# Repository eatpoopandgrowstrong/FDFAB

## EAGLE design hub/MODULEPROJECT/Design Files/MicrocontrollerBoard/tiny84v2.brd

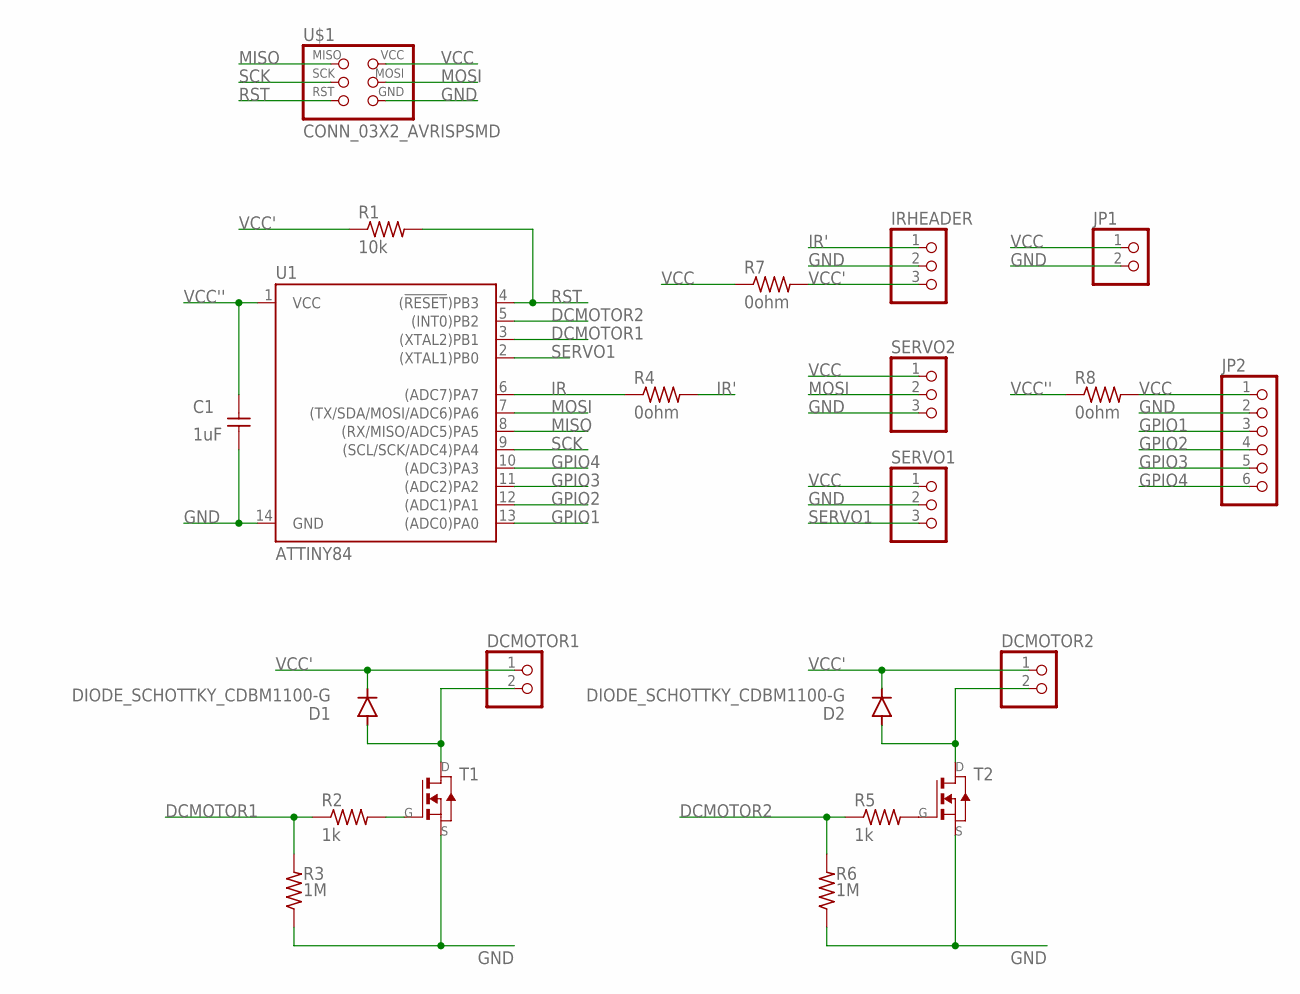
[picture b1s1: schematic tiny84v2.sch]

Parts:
C1: 1uF; C1206FAB
D1, D2: DIODE_SCHOTTKY_CDBM1100-G; MINI-SMA
DCMOTOR1, DCMOTOR2: PINHD-1X2; 1X02
IRHEADER: PINHD-1X3; 1X03
JP1: PINHD-1X2; 1X02
JP2: PINHD-1X6; 1X06
R1: 10k; R1206FAB
R2, R5: 1k; R1206FAB
R3, R6: 1M; R1206FAB
R4, R7, R8: 0ohm; R1206FAB
SERVO1, SERVO2: PINHD-1X3; 1X03
T1, T2: MOSFET_NSOT23; SOT-23
U1: ATTINY84; SO14
U$1: CONN_03X2_AVRISPSMD; 2X03SMD

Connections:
DCMOTOR1: R2.1, R3.2, U1.3 ((XTAL2)PB1)
DCMOTOR2: R5.1, R6.2, U1.5 ((INT0)PB2)
GND: C1.1, IRHEADER.2, JP1.2, JP2.2, R3.1, R6.1, SERVO1.2, SERVO2.3, T1.2 (S), T2.2 (S), U1.14 (GND), U$1.6 (GND)
GPIO1: JP2.3, U1.13 ((ADC0)PA0)
GPIO2: JP2.4, U1.12 ((ADC1)PA1)
GPIO3: JP2.5, U1.11 ((ADC2)PA2)
GPIO4: JP2.6, U1.10 ((ADC3)PA3)
IR: R4.1, U1.6 ((ADC7)PA7)
IR': IRHEADER.1, R4.2
MISO: U1.8 ((RX/MISO/ADC5)PA5), U$1.1 (MISO)
MOSI: SERVO2.2, U1.7 ((TX/SDA/MOSI/ADC6)PA6), U$1.4 (MOSI)
unnamed: D2.ANODE, DCMOTOR2.2, T2.1 (D)
unnamed: D1.ANODE, DCMOTOR1.2, T1.1 (D)
unnamed: R2.2, T1.3 (G)
unnamed: R5.2, T2.3 (G)
RST: R1.2, U1.4 ((!RESET!)PB3), U$1.5 (RST)
SCK: U1.9 ((SCL/SCK/ADC4)PA4), U$1.3 (SCK)
SERVO1: SERVO1.3, U1.2 ((XTAL1)PB0)
VCC: JP1.1, JP2.1, R7.1, R8.2, SERVO1.1, SERVO2.1, U$1.2 (VCC)
VCC': D1.KATHODE, D2.KATHODE, DCMOTOR1.1, DCMOTOR2.1, IRHEADER.3, R1.1, R7.2
VCC'': C1.2, R8.1, U1.1 (VCC)

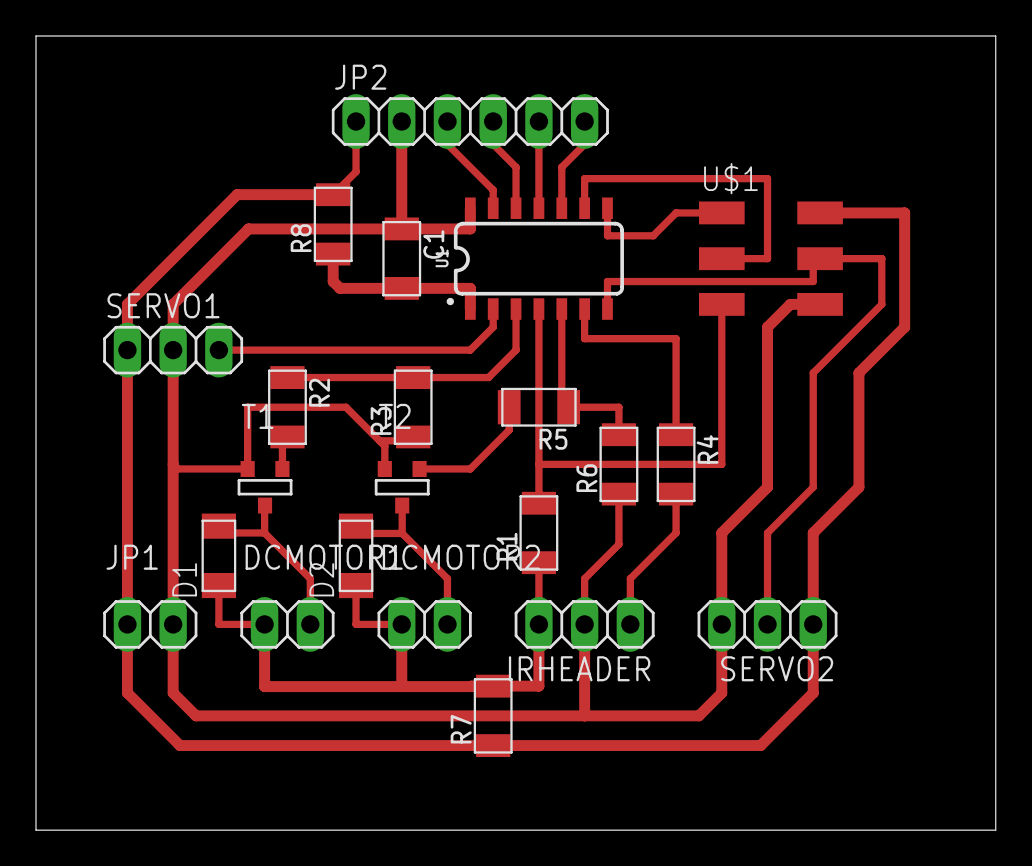
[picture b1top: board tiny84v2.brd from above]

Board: 2 copper layers, 53.3 x 44.1 mm, 22 parts (0 on the bottom side), 21 nets.

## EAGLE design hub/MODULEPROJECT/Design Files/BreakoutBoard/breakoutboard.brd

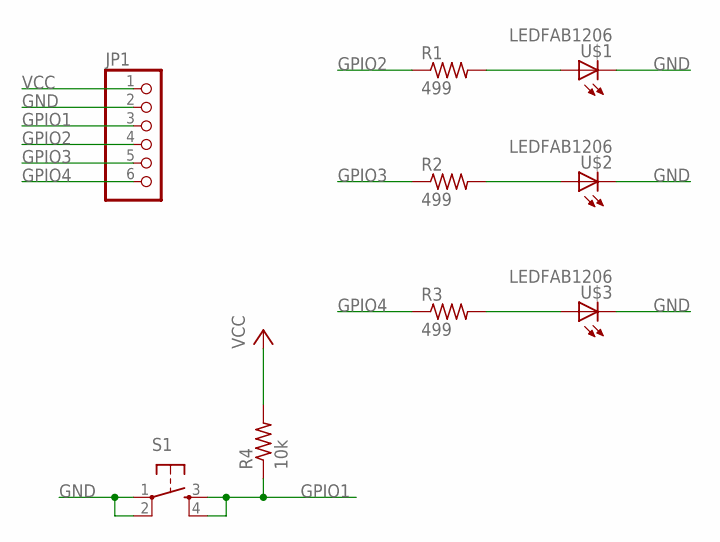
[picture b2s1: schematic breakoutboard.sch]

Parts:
JP1: PINHD-1X6; 1X06
R1, R2, R3: 499; R1206FAB
R4: 10k; R1206FAB
S1: SW_SWITCH_TACTILE_6MM6MM_SWITCH; 6MM_SWITCH
U$1, U$2, U$3: LEDFAB1206; LED1206FAB

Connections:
GND: JP1.2, S1.1, S1.2 (P1), U$1.2 (C), U$2.2 (C), U$3.2 (C)
GPIO1: JP1.3, R4.1, S1.3 (S), S1.4 (S1)
GPIO2: JP1.4, R1.1
GPIO3: JP1.5, R2.1
GPIO4: JP1.6, R3.1
unnamed: R1.2, U$1.1 (A)
unnamed: R2.2, U$2.1 (A)
unnamed: R3.2, U$3.1 (A)
VCC: JP1.1, R4.2

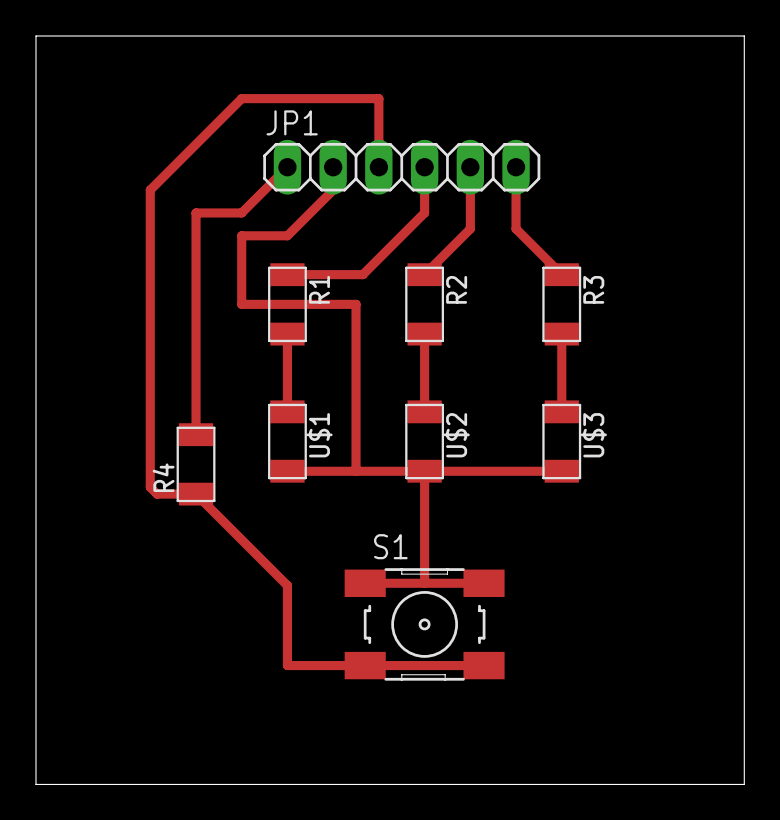
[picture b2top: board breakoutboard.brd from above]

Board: 2 copper layers, 39.4 x 41.6 mm, 9 parts (0 on the bottom side), 9 nets.

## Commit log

2021-01-24 3d machining content and images
2021-01-24 more 3d cnc content and images
2021-01-24 datasheet content and images
2021-01-24 embedded programming files and content
2021-01-24 pushbuttonLED content image and video
2021-01-25 nav bar fix and content
2021-01-25 ino codes as well as content update
2021-01-25 content for processing light bulb aas well as 3d machining stuff
2021-01-25 code for processing serial arduino
2021-01-25 MOAR CONTENT
2021-01-25 updates to images and content
2021-01-25 Slight edit to content as well as 3d machining .nc file
2021-01-25 post processing images and edits to content
2021-01-26 most post processing content and their images
2021-01-28 Embedded programming/processing videos
2021-01-28 updated to show vids
2021-01-28 test fix
2021-01-28 yolo
2021-01-28 Revert "yolo"
    This reverts commit a2d682e73cf3cb537754ce7032bcc7a5690a3578.
2021-01-29 proposal update
2021-01-29 update to nav bar
2021-01-30 3D machining and moldingandcasting content
2021-01-30 moldingandcasting content and videos
2021-01-30 moldandcasting content and images
2021-01-30 more content
2021-01-31 proposal
2021-02-02 molding and casting images and content
2021-02-02 mold release spray
2021-02-06 creation of module project pages
2021-02-06 project electronics start and image
2021-02-06 CONTENT
2021-02-13 content dump
2021-02-13 electronics content dump
2021-02-13 ELECTRONICS CONTENT
2021-02-14 bom and pages
2021-02-15 module project vcarvepro images
2021-02-18 t44 recognition images as well as more content and basic arduino code
2021-02-23 module project images
2021-02-23 module project videos
2021-02-23 cad photos
2021-02-23 ideation images
2021-02-23 module project video
2021-02-24 module project presentation content
2021-02-24 module project fix, removing dedicated page and moving content to homepage
2021-02-26 documentation
2021-02-26 reorganisation of pages
2021-02-26 NAV BAR fix
2021-02-26 formatting
2021-02-26 documentation content
2021-02-26 more documentation content
2021-02-26 image rotation
2021-02-26 content documentation
2021-02-26 fusion 360 3d embedded models
2021-02-26 embed fix
2021-02-26 fusion 360 embed fix
2021-02-26 embed sizing
2021-02-26 moar documentation content
2021-02-26 tiny84 board
2021-02-26 PROJECT DESIGN FILES
2021-02-26 even moar documentation content
2021-02-26 project code
2021-02-26 code writeup
2021-02-26 design file fixes
2021-03-01 module project 3d printing documentation
2021-03-01 module project 3d printing test fit content
2021-03-01 added code for assignments
2021-03-01 programming assignments design files
2021-03-01 assignments
2021-03-04 Set theme jekyll-theme-cayman
2021-03-04 cleaned up the design file section, added some breaks in between
2021-04-13 engrish so bad

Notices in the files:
parts and their libraries:
SparkFun-IC-Microcontroller: Licensing: Creative Commons ShareAlike 4.0 International - https://creativecommons.org/licenses/by-sa/4.0
